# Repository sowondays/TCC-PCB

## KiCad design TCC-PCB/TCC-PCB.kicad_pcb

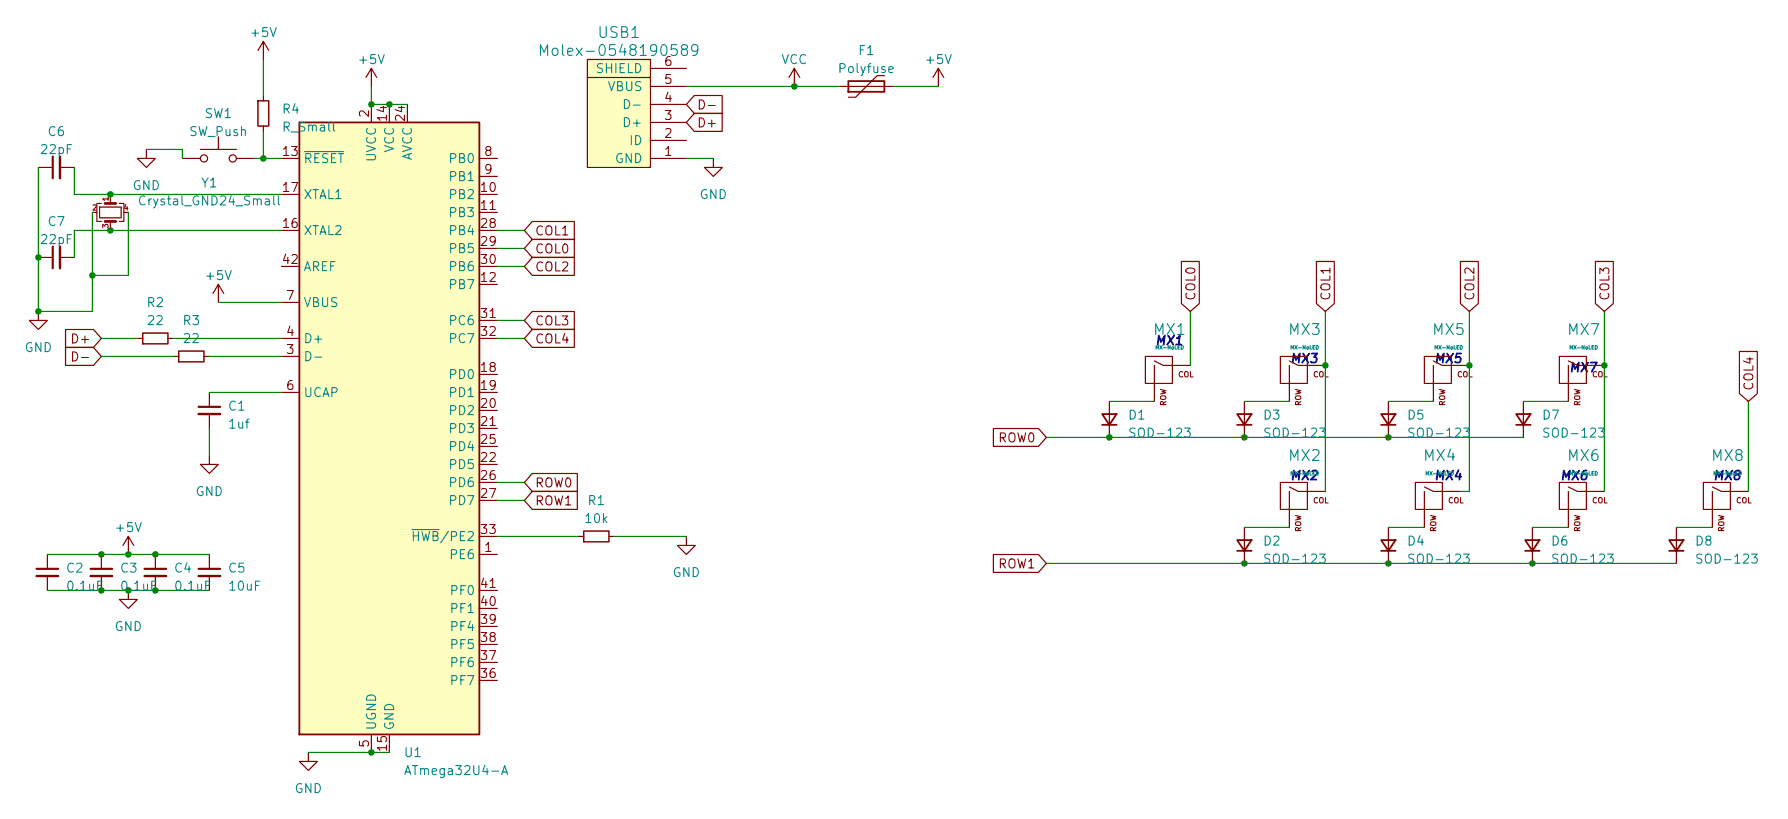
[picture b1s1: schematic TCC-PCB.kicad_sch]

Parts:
C1: 1uf; C_0805_2012Metric
C2, C3, C4: 0.1uF; C_0805_2012Metric
C5: 10uF; C_0805_2012Metric
C6, C7: 22pF; C_0805_2012Metric
D1, D2, D3, D4, D5, D6, D7, D8: SOD-123; D_SOD-123
F1: Polyfuse; Fuse_1206_3216Metric
MX1, MX2, MX3, MX4, MX5, MX6, MX7, MX8: MX-NoLED; MXOnly-1U
R1: 10k; R_0805_2012Metric
R2, R3: 22; R_0805_2012Metric
R4: R_Small; R_0805_2012Metric
SW1: SW_Push; SKQG-1155865
U1: ATmega32U4-A; TQFP-44_10x10mm_P0.8mm
USB1: Molex-0548190589
Y1: Crystal_GND24_Small; Crystal_SMD_3225-4Pin_3.2x2.5mm

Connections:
+5V: C2.1, C3.1, C4.1, C5.1, F1.2, R4.1, U1.2 (UVCC), U1.7 (VBUS), U1.14 (VCC), U1.24 (AVCC), U1.34 (VCC), U1.44 (AVCC)
COL0: MX1.1 (COL), U1.29 (PB5)
COL1: MX2.1 (COL), MX3.1 (COL), U1.28 (PB4)
COL2: MX4.1 (COL), MX5.1 (COL), U1.30 (PB6)
COL3: MX6.1 (COL), MX7.1 (COL), U1.31 (PC6)
COL4: MX8.1 (COL), U1.32 (PC7)
D+: R2.1, USB1.3 (D+)
D-: R3.1, USB1.4 (D-)
GND: C1.2, C2.2, C3.2, C4.2, C5.2, C6.1, C7.1, R1.2, SW1.1, U1.5 (UGND), U1.15 (GND), U1.23 (GND), U1.35 (GND), U1.43 (GND), USB1.1 (GND), Y1.2, Y1.4
unnamed: D1.2 (A), MX1.2 (ROW)
unnamed: D2.2 (A), MX2.2 (ROW)
unnamed: D3.2 (A), MX3.2 (ROW)
unnamed: D4.2 (A), MX4.2 (ROW)
unnamed: D5.2 (A), MX5.2 (ROW)
unnamed: D6.2 (A), MX6.2 (ROW)
unnamed: D7.2 (A), MX7.2 (ROW)
unnamed: D8.2 (A), MX8.2 (ROW)
unnamed: R2.2, U1.4 (D+)
unnamed: R3.2, U1.3 (D-)
unnamed: C1.1, U1.6 (UCAP)
unnamed: C6.2, U1.17 (XTAL1), Y1.1
unnamed: C7.2, U1.16 (XTAL2), Y1.3
unnamed: R1.1, U1.33 (~HWB/PE2)
unnamed: R4.2, SW1.2, U1.13 (~RESET)
ROW0: D1.1 (K), D3.1 (K), D5.1 (K), D7.1 (K), U1.26 (PD6)
ROW1: D2.1 (K), D4.1 (K), D6.1 (K), D8.1 (K), U1.27 (PD7)
VCC: F1.1, USB1.5 (VBUS)

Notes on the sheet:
MX8
MX5
MX3
MX1
MX7
MX6
MX2
MX4

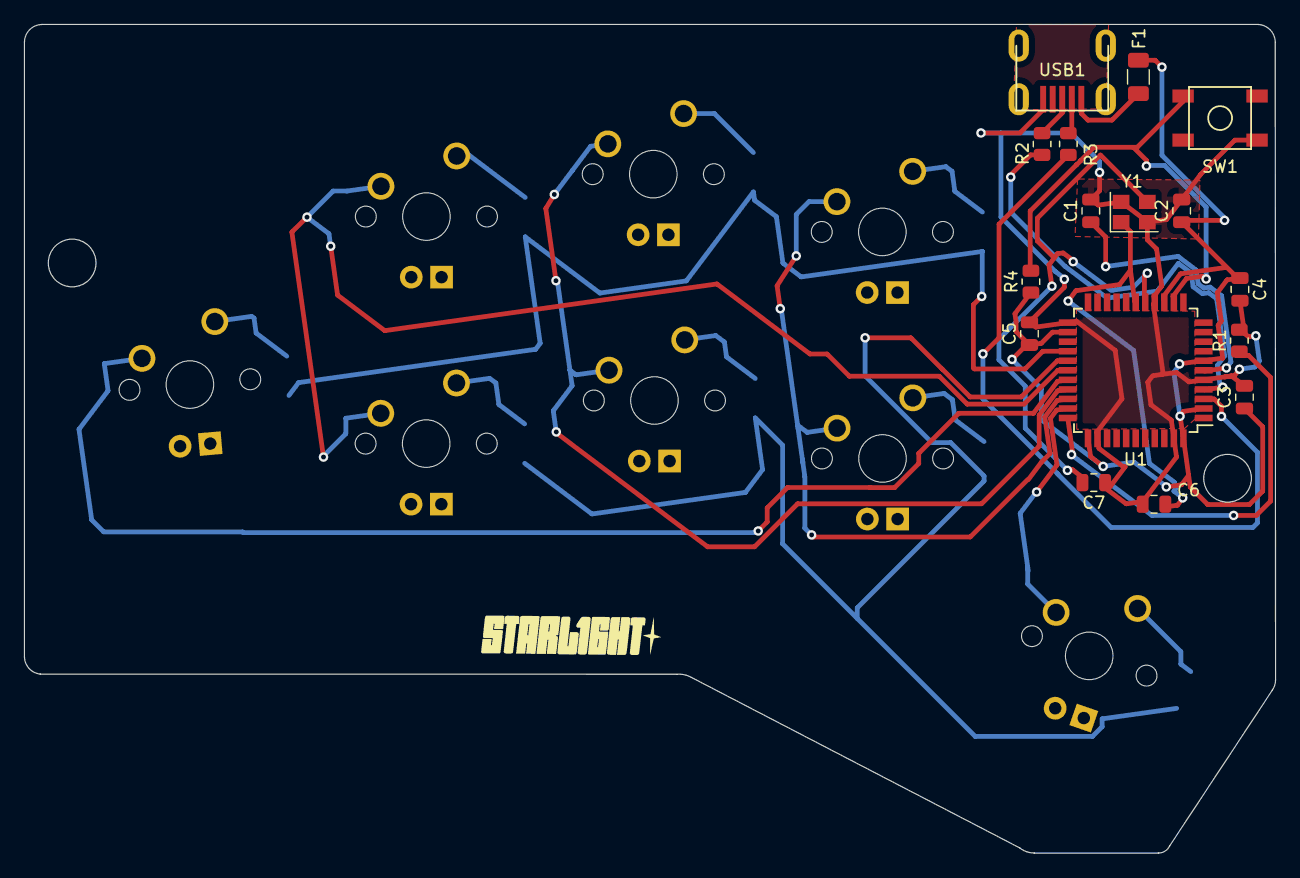
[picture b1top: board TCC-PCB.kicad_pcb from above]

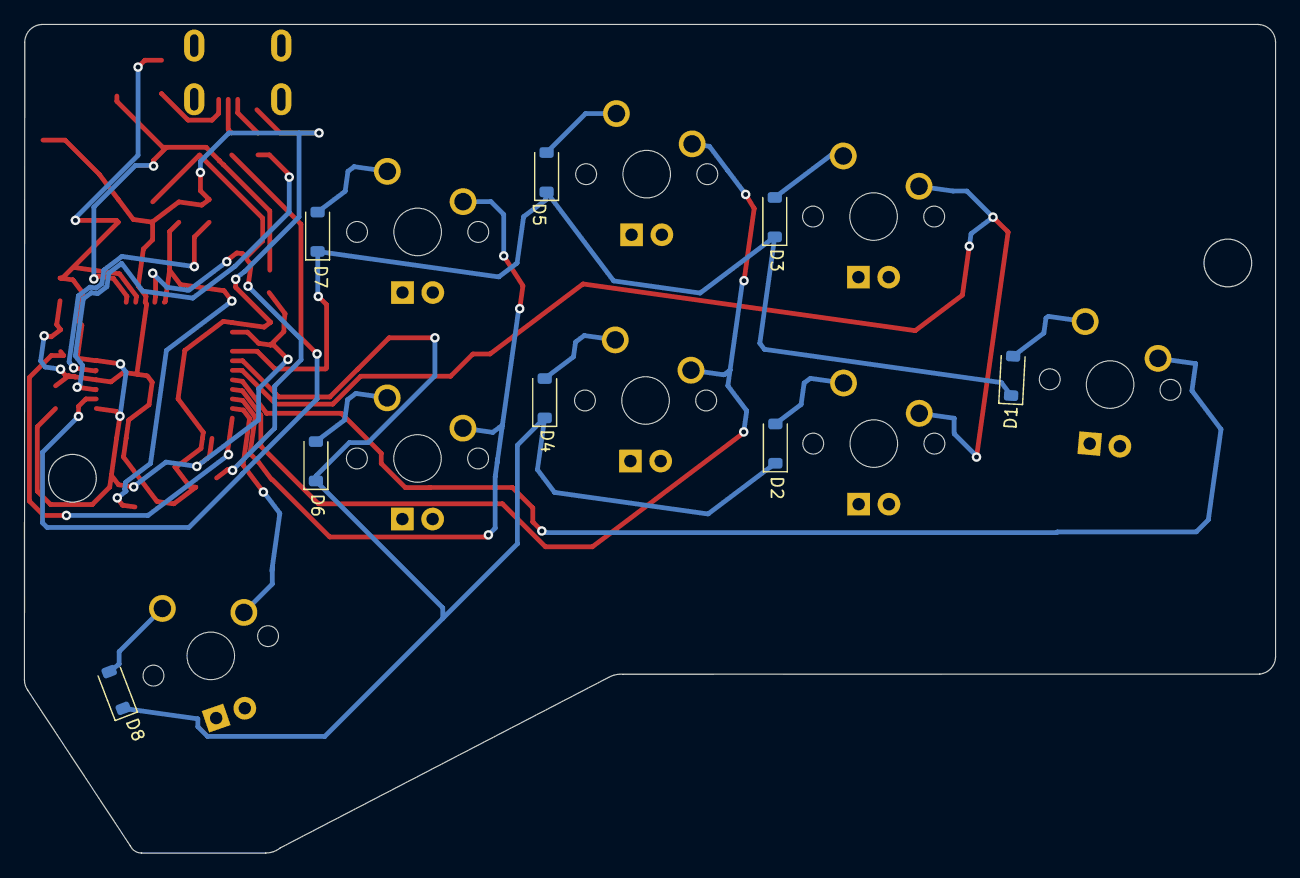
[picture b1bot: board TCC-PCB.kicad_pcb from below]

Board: 2 copper layers, 104.9 x 69.5 mm, 32 parts (8 on the bottom side), 27 nets.

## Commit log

2023-03-09 creating files
2023-03-09 Add submodules
2023-03-10 changing things and schematics ready
2023-03-12 name change
2023-03-16 updates and used footprints
2023-03-20 final changes
